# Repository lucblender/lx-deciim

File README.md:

# lx-deciim

The lx-deciim is a unique 2-channel bitcrusher eurorack module. Conventionals bitcrushers reduce resolution of the input bit by bit starting by the LSB (Least Significant Bit).

The lx-deciim let you select which bit you want to disable. In addition, when a bit is disabled, it can be replaced by a CV input going through a trigger to get a clean '0' '1' value.

The trigger compares the input value against the CV to a reference voltate. This ref value can be set to either 0V or 2.5V from a jumper on the back of the module. In addition, you can also downsample the input signal.

The module is based on the Daisy Seed by Electrosmith.

## Concept

The concept of the module can be described by the following equation:

`audioOut = (audioIn & ~concatSwitch) + (concatTrigger & concatSwitch)`

Considering:

- `audioOut` : 12 bits binary audio output in (integer)
- `audioIn` : 12 bits binary audio input in (integer)
- `concatSwitch` : 12 bits binary value of the concatenation of the switches' value
- `concatTrigger` : 12 bits binary value of the concatenation of the input trigger value

## Bloc diagram

## Specification

- 12 bits 48kHz
- 12 CVs input to trigger audio-rate capable
- 2 inputs eurack level compatible +-5V
- 2 outputs eurack level compatible +-5V
- Downsampling from 48kHz to 1kHz
- Width: 12HP
- Power Consumptions +12V=80mA, -12V=2mA, +5V=0mA

## Repository content

- [Hardware](Hardware/): KiCad Project & Front Panel
  - [Hardware/lx-deciim/](Hardware/lx-deciim/): KiCad Project, Main PCB + Front Panel PCB
  - [Hardware/lx-deciim-front-panel/](Hardware/lx-deciim-front-panel/): SVG design of the front panel
- [Software](Software/): Main software & python script to generate front panel design
  - [Software/lx-deciim-libdaisy/](Software/lx-deciim-libdaisy/): Main software based on LibDaisy
  - [pattern_square_generator.py](Software/pattern_square_generator.py): Main software & python script to generate front panel design

## Hardware

The module consist of 2 PCBs. The main PCB (in reality two PCBs on a panel), and the front panel. The main PCB is really standard 2 layers PCB. After snapping the panel, you can assemble the two PCBs together with the help of male/female header. The front panel is a one layer PCB. I chose matte black solder mask, white silkscreen and ENIG finish on the copper.

All PCB shown in pictures in this repo are manufactured using [PCBWay](https://pcbway.com) services.

PCBWay provides high-quality PCB manufacturing with reliable service and fast turnaround times, making them my first choice for prototyping as seen in this project. They can also make more complex PCB to fit any of your requirements.

## License

This project is licensed under the [CC BY-NC 4.0](https://creativecommons.org/licenses/by-nc/4.0/) License. You may use, modify, and share it for non-commercial purposes.

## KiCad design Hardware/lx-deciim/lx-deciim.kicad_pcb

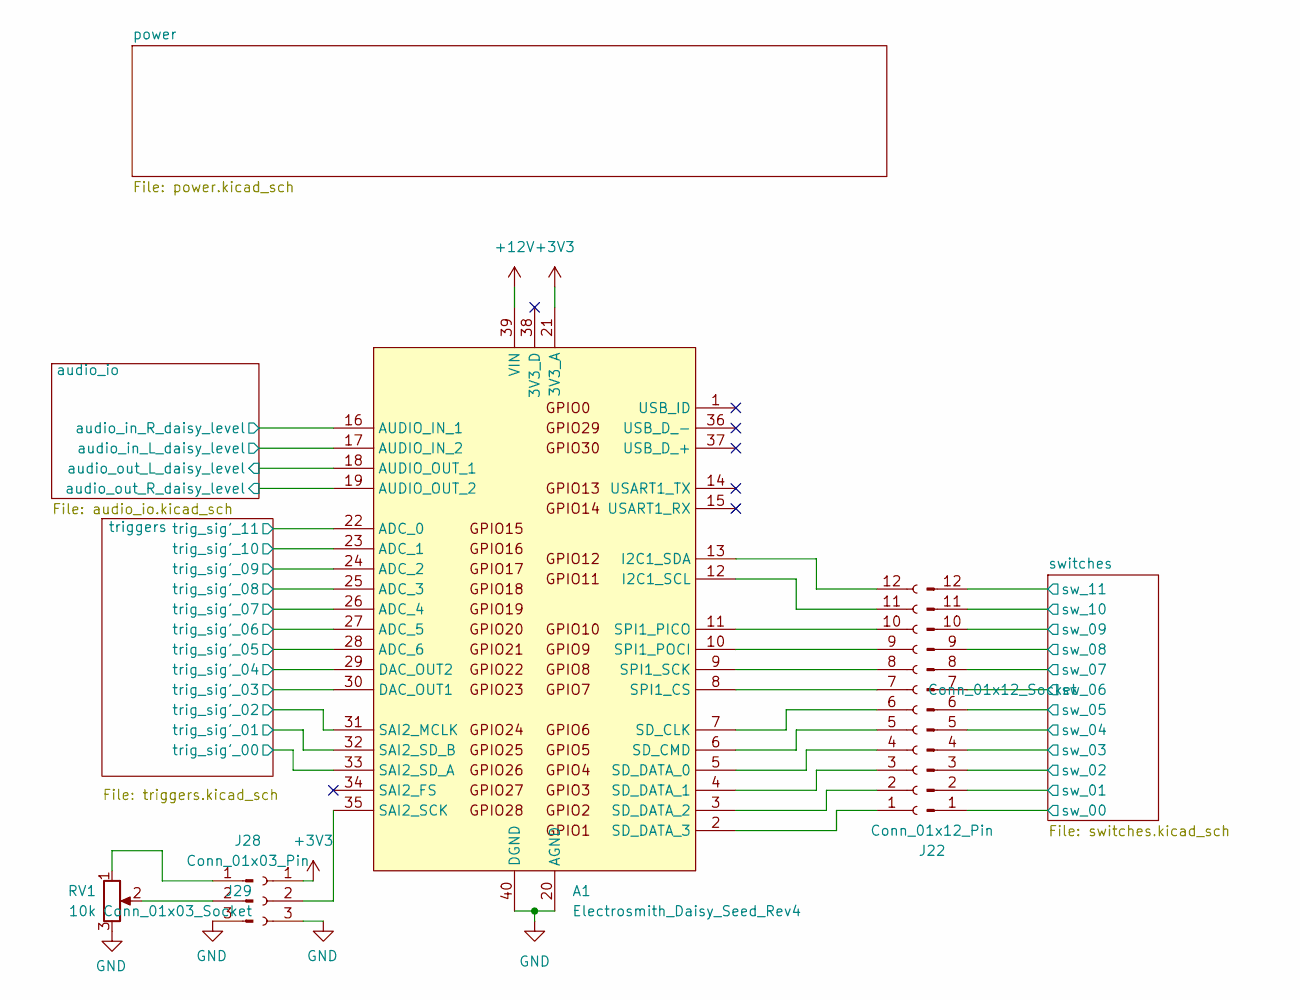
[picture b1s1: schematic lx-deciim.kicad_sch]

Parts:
A1: Electrosmith_Daisy_Seed_Rev4; Electrosmith_Daisy_Seed
J22: Conn_01x12_Pin; PinHeader_1x12_P2.54mm_Vertical
J23: Conn_01x12_Socket; PinSocket_1x12_P2.54mm_Vertical
J28: Conn_01x03_Pin; PinHeader_1x03_P2.54mm_Vertical
J29: Conn_01x03_Socket; PinSocket_1x03_P2.54mm_Vertical
RV1: 10k; Potentiometer_Alpha_RD901F-40-00D_Single_Vertical; Mouser Part Number 311-1940F-15F-B10K

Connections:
+3V3: A1.21 (3V3_A), J29.1
+12V: A1.39 (VIN); also elsewhere on the board
/audio_io/audio_in_L_daisy_level: A1.17 (AUDIO_IN_2); also elsewhere on the board
/audio_io/audio_in_R_daisy_level: A1.16 (AUDIO_IN_1); also elsewhere on the board
/audio_io/audio_out_L_daisy_level: A1.18 (AUDIO_OUT_1); also elsewhere on the board
/audio_io/audio_out_R_daisy_level: A1.19 (AUDIO_OUT_2); also elsewhere on the board
/switches/sw_00: J22.1; also elsewhere on the board
/switches/sw_01: J22.2; also elsewhere on the board
/switches/sw_02: J22.3; also elsewhere on the board
/switches/sw_03: J22.4; also elsewhere on the board
/switches/sw_04: J22.5; also elsewhere on the board
/switches/sw_05: J22.6; also elsewhere on the board
/switches/sw_06: J22.7; also elsewhere on the board
/switches/sw_07: J22.8; also elsewhere on the board
/switches/sw_08: J22.9; also elsewhere on the board
/switches/sw_09: J22.10; also elsewhere on the board
/switches/sw_10: J22.11; also elsewhere on the board
/switches/sw_11: J22.12; also elsewhere on the board
GND: A1.20 (AGND), A1.40 (DGND), J28.3, J29.3, RV1.3; also elsewhere on the board
unnamed: A1.12 (I2C1_SCL), J23.11
unnamed: A1.13 (I2C1_SDA), J23.12
unnamed: A1.35 (SAI2_SCK), J29.2
unnamed: A1.7 (SD_CLK), J23.6
unnamed: A1.6 (SD_CMD), J23.5
unnamed: A1.5 (SD_DATA_0), J23.4
unnamed: A1.4 (SD_DATA_1), J23.3
unnamed: A1.3 (SD_DATA_2), J23.2
unnamed: A1.2 (SD_DATA_3), J23.1
unnamed: A1.8 (SPI1_CS), J23.7
unnamed: A1.11 (SPI1_PICO), J23.10
unnamed: A1.10 (SPI1_POCI), J23.9
unnamed: A1.9 (SPI1_SCK), J23.8
unnamed: J28.1, RV1.1
unnamed: J28.2, RV1.2
trig_sig'_00: A1.33 (SAI2_SD_A); also elsewhere on the board
trig_sig'_01: A1.32 (SAI2_SD_B); also elsewhere on the board
trig_sig'_02: A1.31 (SAI2_MCLK); also elsewhere on the board
trig_sig'_03: A1.30 (DAC_OUT1); also elsewhere on the board
trig_sig'_04: A1.29 (DAC_OUT2); also elsewhere on the board
trig_sig'_05: A1.28 (ADC_6); also elsewhere on the board
trig_sig'_06: A1.27 (ADC_5); also elsewhere on the board
trig_sig'_07: A1.26 (ADC_4); also elsewhere on the board
trig_sig'_08: A1.25 (ADC_3); also elsewhere on the board
trig_sig'_09: A1.24 (ADC_2); also elsewhere on the board
trig_sig'_10: A1.23 (ADC_1); also elsewhere on the board
trig_sig'_11: A1.22 (ADC_0); also elsewhere on the board

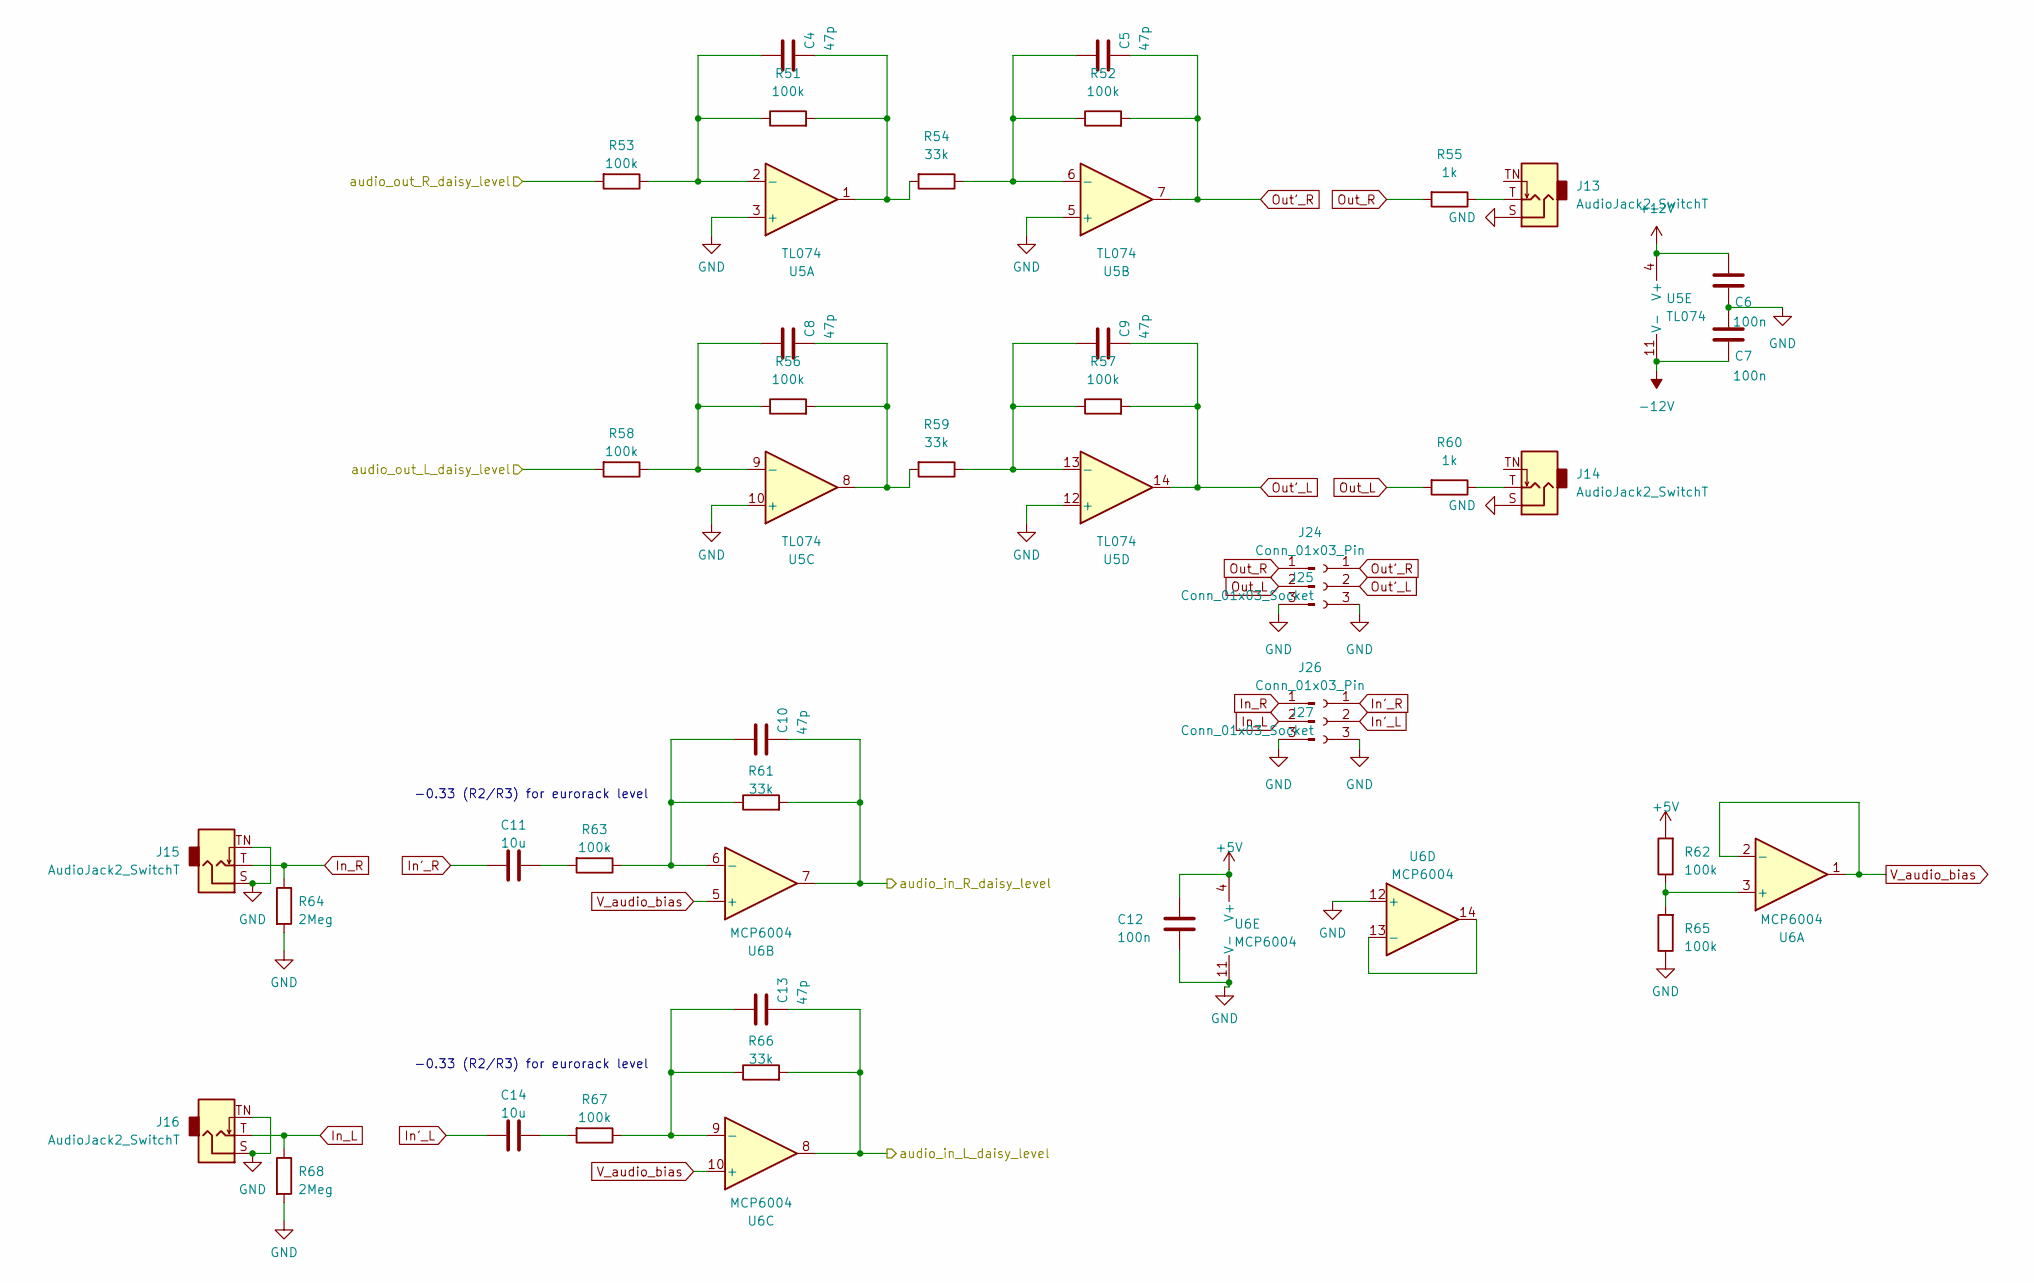
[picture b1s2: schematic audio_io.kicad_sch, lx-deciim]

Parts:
C4, C5, C8, C9, C10, C13: 47p; C_0603_1608Metric; Mouser Part Number 77-VJ0603A470KXJCBC
C6, C7, C12: 100n; C_0603_1608Metric; Mouser Part Number 710-885012206071R
C11, C14: 10u; C_0603_1608Metric; Mouser Part Number 963-BASE168SB5105KT
J13, J14, J15, J16: AudioJack2_SwitchT; PJ301M-12
J24, J26: Conn_01x03_Pin; PinHeader_1x03_P2.54mm_Vertical
J25, J27: Conn_01x03_Socket; PinSocket_1x03_P2.54mm_Vertical
R51, R52, R53, R56, R57, R58, R62, R63, R65, R67: 100k; R_0603_1608Metric; Mouser Part Number 603-AC0603JR-07100KL
R54, R59, R61, R66: 33k; R_0603_1608Metric; Mouser Part Number 660-RK73H1JTTD3302F
R55, R60: 1k; R_0603_1608Metric; Mouser Part Number 660-RK73H1JTTD1001F
R64, R68: 2Meg; R_0603_1608Metric; Mouser Part Number 660-RK73H1JTTDD2004F
U5: TL074; SOP50P326X110-14N; Mouser Part Number 595-TL074HIDYYR
U6: MCP6004; SOIC-14_3.9x8.7mm_P1.27mm; Mouser Part Number 579-MCP6004-I/SL

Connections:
+5V: C12.1, R62.2, U6.4 (V+); also elsewhere on the board
+12V: C6.1, U5.4 (V+); also elsewhere on the board
-12V: C7.2, U5.11 (V-); also elsewhere on the board
/audio_io/audio_in_L_daisy_level: C13.2, R66.2, U6.8; also elsewhere on the board
/audio_io/audio_in_R_daisy_level: C10.2, R61.2, U6.7; also elsewhere on the board
/audio_io/audio_out_L_daisy_level: R58.2; also elsewhere on the board
/audio_io/audio_out_R_daisy_level: R53.2; also elsewhere on the board
GND: C6.2, C7.1, C12.2, J13.S, J14.S, J15.S, J15.TN, J16.S, J16.TN, J24.3, J25.3, J26.3, J27.3, R64.2, R65.1, R68.2, U5.3 (+), U5.5 (+), U5.10 (+), U5.12 (+), U6.11 (V-), U6.12 (+); also elsewhere on the board
In'_L: C14.1, J27.2
In'_R: C11.1, J27.1
In_L: J16.T, J26.2, R68.1
In_R: J15.T, J26.1, R64.1
unnamed: C4.2, R51.2, R54.2, U5.1
unnamed: C8.2, R56.2, R59.2, U5.8
unnamed: C11.2, R63.2
unnamed: C14.2, R67.2
unnamed: J13.T, R55.1
unnamed: J14.T, R60.1
unnamed: C4.1, R51.1, R53.1, U5.2 (-)
unnamed: C5.1, R52.1, R54.1, U5.6 (-)
unnamed: C8.1, R56.1, R58.1, U5.9 (-)
unnamed: C9.1, R57.1, R59.1, U5.13 (-)
unnamed: R62.1, R65.2, U6.3 (+)
unnamed: C10.1, R61.1, R63.1, U6.6 (-)
unnamed: C13.1, R66.1, R67.1, U6.9 (-)
unnamed: U6.13 (-), U6.14
Out'_L: C9.2, J25.2, R57.2, U5.14
Out'_R: C5.2, J25.1, R52.2, U5.7
Out_L: J24.2, R60.2
Out_R: J24.1, R55.2
V_audio_bias: U6.1, U6.2 (-), U6.5 (+), U6.10 (+)

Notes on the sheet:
-0.33 (R2/R3) for eurorack level

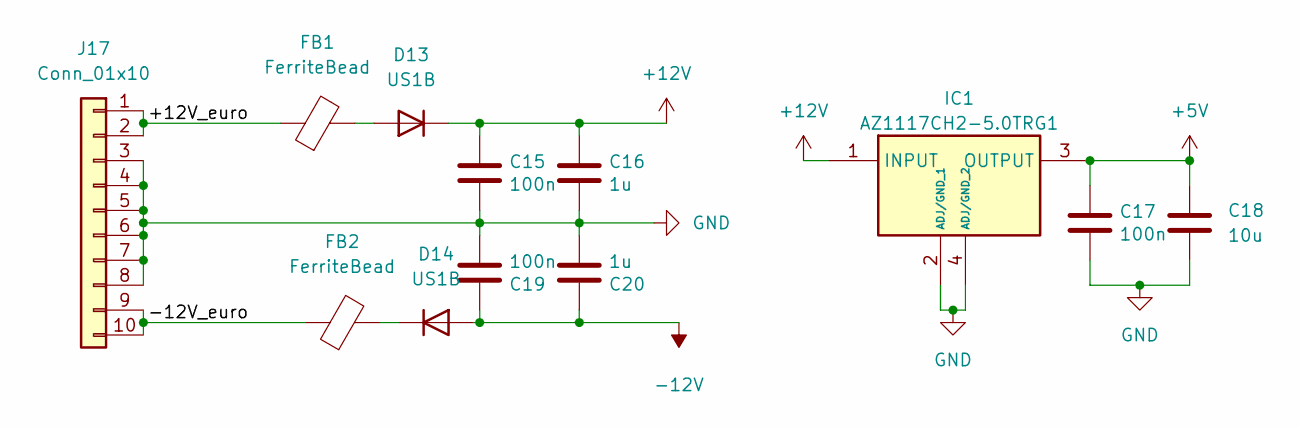
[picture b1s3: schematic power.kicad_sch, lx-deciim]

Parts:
C15, C17, C19: 100n; C_0603_1608Metric; Mouser Part Number 710-885012206071R; LCSC C14663
C16, C20: 1u; C_0603_1608Metric; Mouser Part Number 187-CL10B105KO8NNWC; LCSC C14663
C18: 10u; C_0603_1608Metric; Mouser Part Number 963-BASE168SB5105KT
D13, D14: US1B; D_SMA; Mouser Part Number 637-US1B
FB1, FB2: FerriteBead; L_0805_2012Metric; Mouser Part Number 710-742792031
IC1: AZ1117CH2-5.0TRG1; SOT230P700X180-4N; Mouser Part Number 621-AZ1117CH2-5.0TRG
J17: Conn_01x10; PinHeader_2x05_P2.54mm_Vertical_SMD; Mouser Part Number 200-TSM10501LDVPTR

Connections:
+5V: C17.1, C18.2, IC1.3 (OUTPUT); also elsewhere on the board
+12V: C15.1, C16.1, D13.1 (K), IC1.1 (INPUT); also elsewhere on the board
-12V: C19.1, C20.1, D14.2 (A); also elsewhere on the board
/power/+12V_euro: FB1.1, J17.1, J17.2
/power/-12V_euro: FB2.1, J17.9, J17.10
GND: C15.2, C16.2, C17.2, C18.1, C19.2, C20.2, IC1.2 (ADJ/GND_1), IC1.4 (ADJ/GND_2), J17.3, J17.4, J17.5, J17.6, J17.7, J17.8; also elsewhere on the board
unnamed: D13.2 (A), FB1.2
unnamed: D14.1 (K), FB2.2

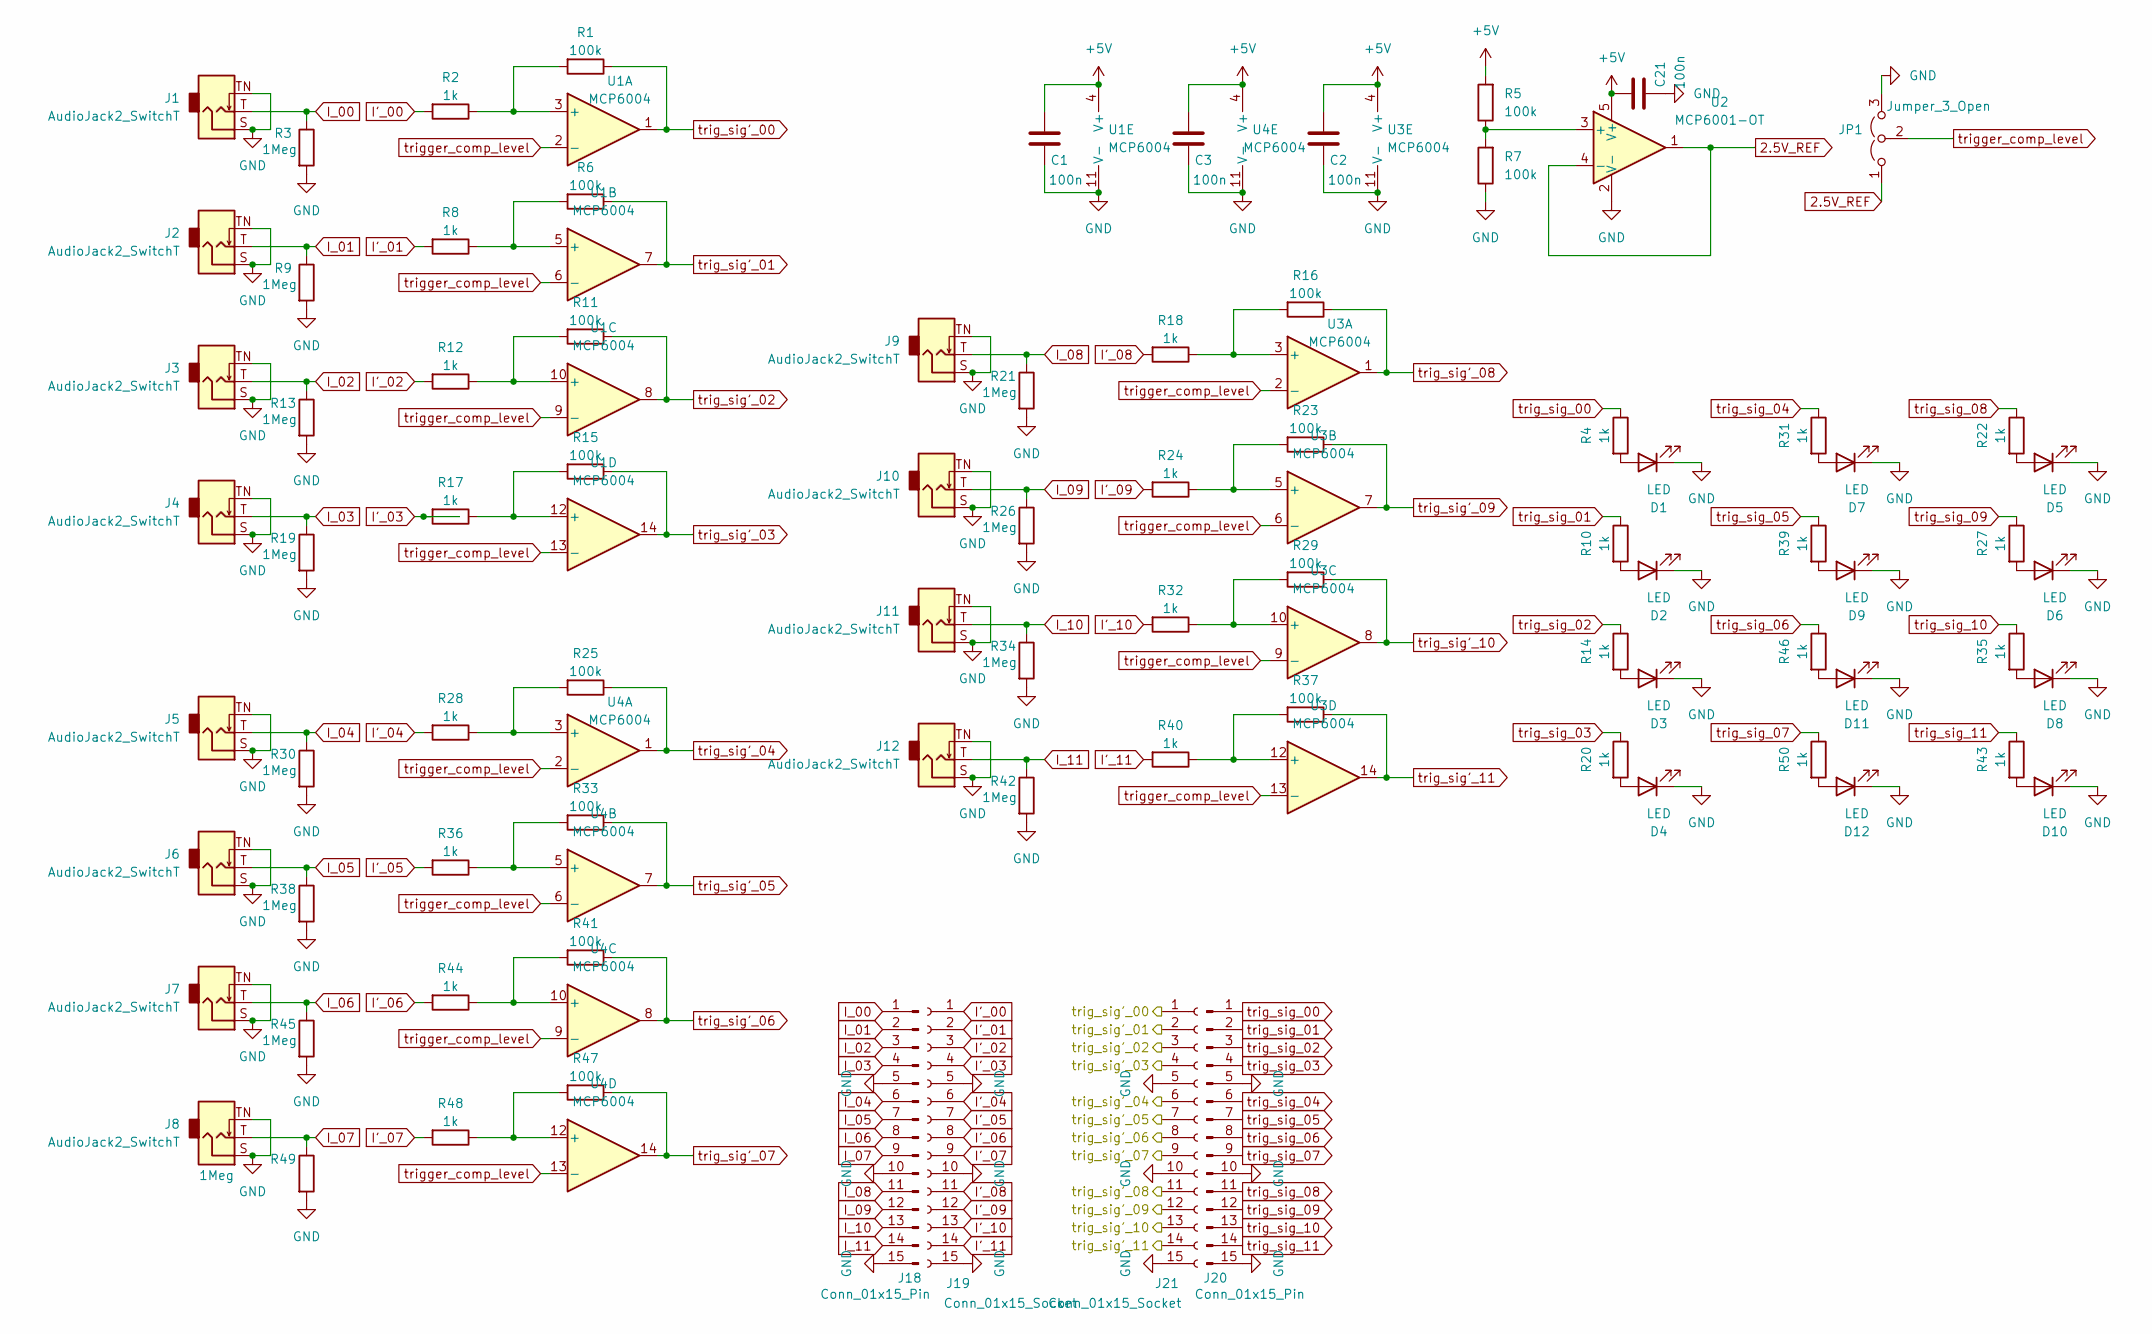
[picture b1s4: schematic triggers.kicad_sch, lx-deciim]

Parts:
C1, C2, C3, C21: 100n; C_0603_1608Metric; Mouser Part Number 710-885012206071R
D1, D2, D3, D4, D5, D6, D7, D8, D9, D10, D11, D12: LED; LED_D3.0mm; Mouser Part Number 859-LTL1CHTBK5
J1, J2, J3, J4, J5, J6, J7, J8, J9, J10, J11, J12: AudioJack2_SwitchT; PJ301M-12
J18, J20: Conn_01x15_Pin; PinHeader_1x15_P2.54mm_Vertical; Mouser Part Number 737-PH1-40-UA
J19, J21: Conn_01x15_Socket; PinSocket_1x15_P2.54mm_Vertical; Mouser Part Number 737-SMC-1-40-1-GT
JP1: Jumper_3_Open; PinHeader_1x03_P2.54mm_Vertical; Mouser Part Number 737-MSA-G
R1, R5, R6, R7, R11, R15, R16, R23, R25, R29, R33, R37, R41, R47: 100k; R_0603_1608Metric; Mouser Part Number 603-AC0603JR-07100KL
R2, R4, R8, R10, R12, R14, R17, R18, R20, R22, R24, R27, R28, R31, R32, R35, R36, R39, R40, R43, R44, R46, R48, R50: 1k; R_0603_1608Metric; Mouser Part Number 660-RK73H1JTTD1001F
R3, R9, R13, R19, R21, R26, R30, R34, R38, R42, R45, R49: 1Meg; R_0603_1608Metric; Mouser Part Number 71-CRCW0603-1.0M-E3
U1, U3, U4: MCP6004; SOIC-14_3.9x8.7mm_P1.27mm; Mouser Part Number 579-MCP6004-I/SL
U2: MCP6001-OT; SOT-23-5; Mouser Part Number 579-MCP6001RT-I/OT

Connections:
2.5V_REF: JP1.1 (A), U2.1, U2.4 (-)
+5V: C1.1, C2.1, C3.1, C21.1, R5.2, U1.4 (V+), U2.5 (V+), U3.4 (V+), U4.4 (V+); also elsewhere on the board
GND: C1.2, C2.2, C3.2, C21.2, D1.1 (K), D2.1 (K), D3.1 (K), D4.1 (K), D5.1 (K), D6.1 (K), D7.1 (K), D8.1 (K), D9.1 (K), D10.1 (K), D11.1 (K), D12.1 (K), J1.S, J1.TN, J2.S, J2.TN, J3.S, J3.TN, J4.S, J4.TN, J5.S, J5.TN, J6.S, J6.TN, J7.S, J7.TN, J8.S, J8.TN, J9.S, J9.TN, J10.S, J10.TN, J11.S, J11.TN, J12.S, J12.TN, J18.5, J18.10, J18.15, J19.5, J19.10, J19.15, J20.5, J20.10, J20.15, J21.5, J21.10, J21.15, JP1.3 (B), R3.2, R7.1, R9.2, R13.2, R19.2, R21.2, R26.2, R30.2, R34.2, R38.2, R42.2, R45.2, R49.2, U1.11 (V-), U2.2 (V-), U3.11 (V-), U4.11 (V-); also elsewhere on the board
I'_00: J19.1, R2.2
I'_01: J19.2, R8.2
I'_02: J19.3, R12.2
I'_03: J19.4, R17.2
I'_04: J19.6, R28.2
I'_05: J19.7, R36.2
I'_06: J19.8, R44.2
I'_07: J19.9, R48.2
I'_08: J19.11, R18.2
I'_09: J19.12, R24.2
I'_10: J19.13, R32.2
I'_11: J19.14, R40.2
I_00: J1.T, J18.1, R3.1
I_01: J2.T, J18.2, R9.1
I_02: J3.T, J18.3, R13.1
I_03: J4.T, J18.4, R19.1
I_04: J5.T, J18.6, R30.1
I_05: J6.T, J18.7, R38.1
I_06: J7.T, J18.8, R45.1
I_07: J8.T, J18.9, R49.1
I_08: J9.T, J18.11, R21.1
I_09: J10.T, J18.12, R26.1
I_10: J11.T, J18.13, R34.1
I_11: J12.T, J18.14, R42.1
unnamed: D1.2 (A), R4.2
unnamed: D2.2 (A), R10.2
unnamed: D3.2 (A), R14.2
unnamed: D4.2 (A), R20.2
unnamed: D5.2 (A), R22.2
unnamed: D6.2 (A), R27.2
unnamed: D7.2 (A), R31.2
unnamed: D8.2 (A), R35.2
unnamed: D9.2 (A), R39.2
unnamed: D10.2 (A), R43.2
unnamed: D11.2 (A), R46.2
unnamed: D12.2 (A), R50.2
unnamed: R1.2, R2.1, U1.3 (+)
unnamed: R6.2, R8.1, U1.5 (+)
unnamed: R11.2, R12.1, U1.10 (+)
unnamed: R15.2, R17.1, U1.12 (+)
unnamed: R5.1, R7.2, U2.3 (+)
unnamed: R16.2, R18.1, U3.3 (+)
unnamed: R23.2, R24.1, U3.5 (+)
unnamed: R29.2, R32.1, U3.10 (+)
unnamed: R37.2, R40.1, U3.12 (+)
unnamed: R25.2, R28.1, U4.3 (+)
unnamed: R33.2, R36.1, U4.5 (+)
unnamed: R41.2, R44.1, U4.10 (+)
unnamed: R47.2, R48.1, U4.12 (+)
trig_sig'_00: J21.1, R1.1, U1.1; also elsewhere on the board
trig_sig'_01: J21.2, R6.1, U1.7; also elsewhere on the board
trig_sig'_02: J21.3, R11.1, U1.8; also elsewhere on the board
trig_sig'_03: J21.4, R15.1, U1.14; also elsewhere on the board
trig_sig'_04: J21.6, R25.1, U4.1; also elsewhere on the board
trig_sig'_05: J21.7, R33.1, U4.7; also elsewhere on the board
trig_sig'_06: J21.8, R41.1, U4.8; also elsewhere on the board
trig_sig'_07: J21.9, R47.1, U4.14; also elsewhere on the board
trig_sig'_08: J21.11, R16.1, U3.1; also elsewhere on the board
trig_sig'_09: J21.12, R23.1, U3.7; also elsewhere on the board
trig_sig'_10: J21.13, R29.1, U3.8; also elsewhere on the board
trig_sig'_11: J21.14, R37.1, U3.14; also elsewhere on the board
trig_sig_00: J20.1, R4.1
trig_sig_01: J20.2, R10.1
trig_sig_02: J20.3, R14.1
trig_sig_03: J20.4, R20.1
trig_sig_04: J20.6, R31.1
trig_sig_05: J20.7, R39.1
trig_sig_06: J20.8, R46.1
trig_sig_07: J20.9, R50.1
trig_sig_08: J20.11, R22.1
trig_sig_09: J20.12, R27.1
trig_sig_10: J20.13, R35.1
trig_sig_11: J20.14, R43.1
trigger_comp_level: JP1.2 (C), U1.2 (-), U1.6 (-), U1.9 (-), U1.13 (-), U3.2 (-), U3.6 (-), U3.9 (-), U3.13 (-), U4.2 (-), U4.6 (-), U4.9 (-), U4.13 (-)

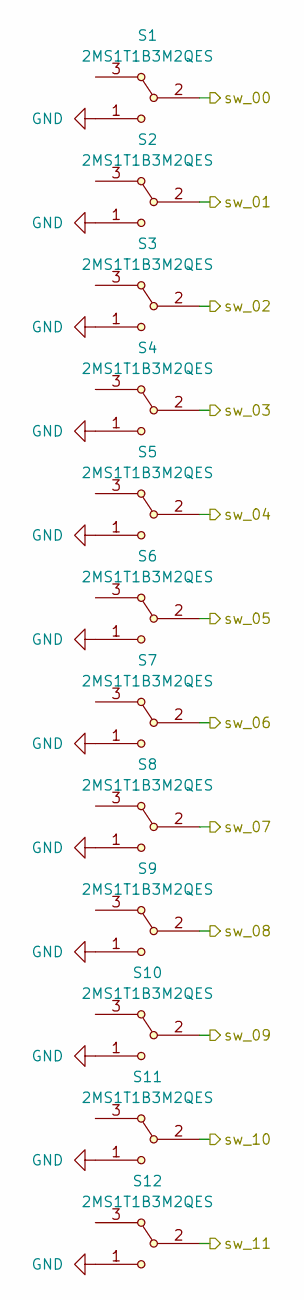
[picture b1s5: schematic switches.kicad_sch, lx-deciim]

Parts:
S1, S2, S3, S4, S5, S6, S7, S8, S9, S10, S11, S12: 2MS1T1B3M2QES; Mouser Part Number 118-2MS1T1B3M2QES

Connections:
/switches/sw_00: S1.2; also elsewhere on the board
/switches/sw_01: S2.2; also elsewhere on the board
/switches/sw_02: S3.2; also elsewhere on the board
/switches/sw_03: S4.2; also elsewhere on the board
/switches/sw_04: S5.2; also elsewhere on the board
/switches/sw_05: S6.2; also elsewhere on the board
/switches/sw_06: S7.2; also elsewhere on the board
/switches/sw_07: S8.2; also elsewhere on the board
/switches/sw_08: S9.2; also elsewhere on the board
/switches/sw_09: S10.2; also elsewhere on the board
/switches/sw_10: S11.2; also elsewhere on the board
/switches/sw_11: S12.2; also elsewhere on the board
GND: S1.1, S2.1, S3.1, S4.1, S5.1, S6.1, S7.1, S8.1, S9.1, S10.1, S11.1, S12.1; also elsewhere on the board

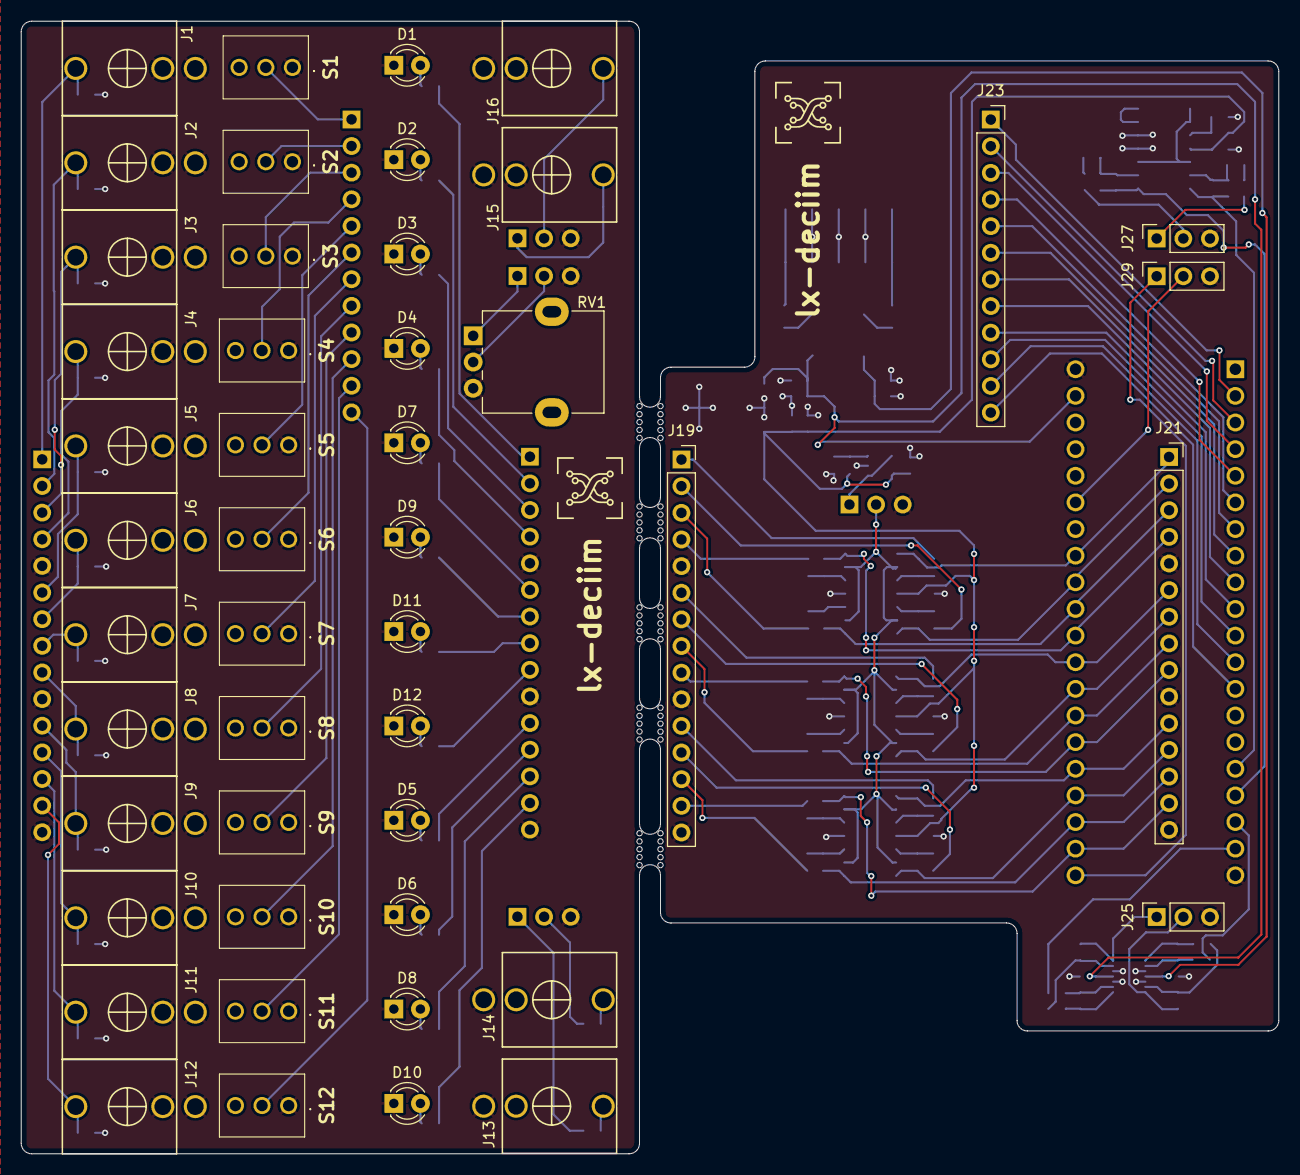
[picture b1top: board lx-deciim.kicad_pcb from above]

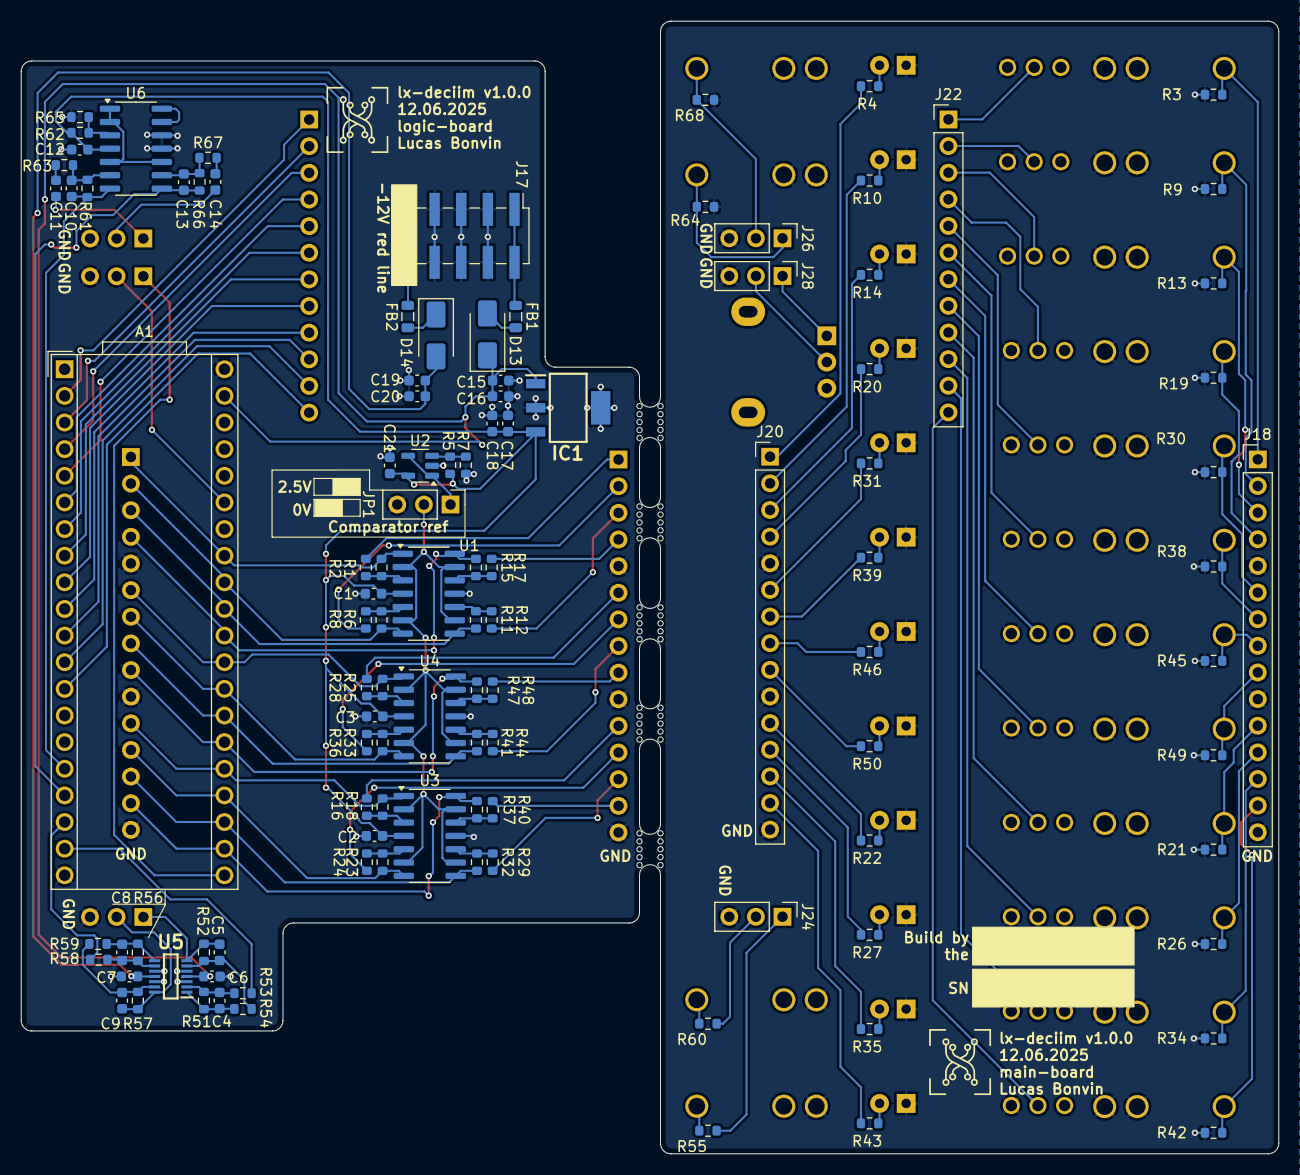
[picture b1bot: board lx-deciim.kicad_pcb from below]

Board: 2 copper layers, 119.9 x 108.0 mm, 156 parts (109 on the bottom side), 138 nets.

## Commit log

2025-06-10 doc: add gitignore and lfs
2025-06-10 feature: add kicad libraries
2025-06-10 feature: first draft of schematic and pcb
2025-06-11 feature: first draft routing
2025-06-12 feature: clean routing
2025-06-12 feature: add pattern_square_generator and front pannel
2025-06-12 feature: prep files for export (fill bom, gerber)
2025-06-17 feature: add demo test ino code
2025-06-17 fix: fix mouser part number on schematic + fill page settings
2025-06-17 feature: add libdaisy blank project
2025-06-17 feature: add bloc diagram
2025-06-17 fix: fix bloc diagram background and size
2025-06-17 fix: fix svg text alignment
2025-06-19 feature: add DownSampler class, port code to libdaisy
2025-06-20 feature: add digital read, put analog read in func
    prepare code for module with todo comment
2025-07-01 feature: modify code to pass to hardware
2025-07-02 fix: fix some unstabilities
2025-07-02 fix: remove unused var
2025-07-02 feature: force out of trigger to 0 if switch is disabled to turn off led
2025-07-02 fix: no delay, remove forcing trigger to 0, cause no more reading of it
2025-07-03 fix: put read analog in AudioCallback
2025-07-03 feature: add readme text
2025-07-03 fix: fix readme error
2025-07-03 fix: fix downsampling error when sampleIndex repass to 0
2025-07-08 feature: funky blinking led boot sequence
2025-09-02 doc: add picture of the module
2025-09-02 fix: remove wrong project name

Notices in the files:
Hardware/lx-deciim/audio_io.kicad_sch:
This project is licensed under the CC BY-NC 4.0 License.
